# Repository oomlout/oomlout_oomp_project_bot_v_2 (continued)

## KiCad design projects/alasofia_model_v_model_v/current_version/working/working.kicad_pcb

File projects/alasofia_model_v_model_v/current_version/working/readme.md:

# model_v
 
## summary 
* id: alasofia_model_v_model_v
* user: alasofia
* name: model_v
* board: model_v
* repo: https://github.com/Alasofia/model-v
* src_file_repo_kicad_pcb: model-v.kicad_pcb
* src_file_repo_kicad_pcb_link: https://github.com/Alasofia/model-v/tree/main/model-v.kicad_pcb

* src_file_repo_sch: 
* src_file_repo_sch_link: https://github.com/Alasofia/model-v/tree/main/
* full details link: https://github.com/oomlout/oomlout_oomp_project_bot_v_2/tree/main/projects/alasofia_model_v_model_v/current_version/working  

## schematic  
  
[schematic (pdf)](working_schematic.pdf) 

## pcb  

[board (pdf)](working.pdf)  

## working_bom
| Id | Designator | Footprint | Quantity | Designation | Supplier and ref |  | None | 
| --- | --- | --- | --- | --- | --- | --- | --- | 
| 1 | K_42 | MXOnly-2.25U-ReversedStabilizers-NoLED | 1 | KEYSW |  |  | [''] | 
| 2 | K_37,K_13,K_47,K_39 | MXOnly-1.25U-NoLED | 4 | KEYSW |  |  | [''] | 
| 3 | K_6,K_32,K_50,K_48,K_18,K_31,K_20,K_22,K_33,K_30,K_7,K_15,K_17,K_49,K_26,K_36,K_8,K_2,K_11,K_5,K_9,K_1,K_10,K_16,K_14,K_35,K_34,K_46,K_40,K_28,K_3,K_38,K_29,K_21,K_27,K_23,K_19,K_4 | MXOnly-1U-NoLED | 38 | KEYSW |  |  | [''] | 
| 4 | K_44 | MXOnly-2U-ReversedStabilizers-NoLED | 1 | KEYSW |  |  | [''] | 
| 5 | K_12,K_25 | MXOnly-1.75U-NoLED | 2 | KEYSW |  |  | [''] | 
| 6 | K_41,K_45 | MXOnly-3U-ReversedStabilizers-NoLED | 2 | KEYSW |  |  | [''] | 
| 7 | K_24 | MXOnly-1.5U-NoLED | 1 | KEYSW |  |  | [''] | 
| 8 | K_43 | MXOnly-6.25U-ReversedStabilizers-NoLED | 1 | KEYSW |  |  | [''] | 
| 9 | SW1 | SW_Push_SPST_NO_Alps_SKRK | 1 | SW_Push |  |  | [''] | 
| 10 | D_12,D_36,D_46,D_44,D_14,D_20,D_10,D_22,D_13,D_38,D_33,D_45,D_6,D_32,D_2,D_39,D_11,D_37,D_30,D_27,D_18,D_24,D_42,D_17,D_23,D_41,D_9,D_8,D_29,D_31,D_15,D_16,D_1,D_3,D_28,D_7,D_4,D_5,D_19,D_34,D_25,D_21,D_43,D_35,D_40,D_26 | D_SOD-123 | 46 | D |  |  | [''] | 
| 11 | F1 | Fuse_1206_3216Metric | 1 | 500mA |  |  | [''] | 
| 12 | U2 | SOT143B | 1 | PRTR5V0U2X |  |  | [''] | 
| 13 | USB1 | HRO-TYPE-C-31-M-12-Assembly | 1 | HRO-TYPE-C-31-M-12 |  |  | [''] | 
| 14 | R4,R3 | R_0603_1608Metric | 2 | 22 |  |  | [''] | 
| 15 | R2,R1 | R_0603_1608Metric | 2 | 5.1k |  |  | [''] | 
| 16 | C2,C3,C4,C5,C6 | C_0603_1608Metric | 5 | 0.1uF |  |  | [''] | 
| 17 | C7 | C_0603_1608Metric | 1 | 1uF |  |  | [''] | 
| 18 | C8,C9 | C_0603_1608Metric | 2 | 22pF |  |  | [''] | 
| 19 | Y1 | Crystal_SMD_3225-4Pin_3.2x2.5mm | 1 | 16MHz |  |  | [''] | 
| 20 | U1 | QFN-44-1EP_7x7mm_P0.5mm_EP5.2x5.2mm | 1 | ATmega32U4-MU |  |  | [''] | 
| 21 | C1 | C_0603_1608Metric | 1 | 10uF |  |  | [''] | 
| 22 | R5,R6 | R_0603_1608Metric | 2 | 10k |  |  | [''] | 
| 23 | G*** | model-v | 1 | LOGO |  |  | [''] | 

## bom_schematic
| Ref | Qnty | Value | Cmp name | Footprint | Description | Vendor | DNP | 
| --- | --- | --- | --- | --- | --- | --- | --- | 
| C1 | 1 | 10uF | C_Small | Capacitor_SMD:C_0603_1608Metric | Unpolarized capacitor, small symbol |  |  | 
| C2, C3, C4, C5, C6 | 5 | 0.1uF | C_Small | Capacitor_SMD:C_0603_1608Metric | Unpolarized capacitor, small symbol |  |  | 
| C7 | 1 | 1uF | C_Small | Capacitor_SMD:C_0603_1608Metric | Unpolarized capacitor, small symbol |  |  | 
| C8, C9 | 2 | 22pF | C_Small | Capacitor_SMD:C_0603_1608Metric | Unpolarized capacitor, small symbol |  |  | 
| D_1, D_2, D_3, D_4, D_5, D_6, D_7, D_8, D_9, D_10, D_11, D_12, D_13, D_14, D_15, D_16, D_17, D_18, D_19, D_20, D_21, D_22, D_23, D_24, D_25, D_26, D_27, D_28, D_29, D_30, D_31, D_32, D_33, D_34, D_35, D_36, D_37, D_38, D_39, D_40, D_41, D_42, D_43, D_44, D_45, D_46 | 46 | D | D_Small | Diode_SMD:D_SOD-123 | Diode, small symbol |  |  | 
| F1 | 1 | 500mA | Polyfuse_Small | Fuse:Fuse_1206_3216Metric | Resettable fuse, polymeric positive temperature coefficient, small symbol |  |  | 
| K_1, K_2, K_3, K_4, K_5, K_6, K_7, K_8, K_9, K_10, K_11, K_14, K_15, K_16, K_17, K_18, K_19, K_20, K_21, K_22, K_23, K_26, K_27, K_28, K_29, K_30, K_31, K_32, K_33, K_34, K_35, K_36, K_38, K_40, K_46, K_48, K_49, K_50 | 38 | KEYSW | MX-NoLED | MX_Only:MXOnly-1U-NoLED |  |  |  | 
| K_12, K_25 | 2 | KEYSW | MX-NoLED | MX_Only:MXOnly-1.75U-NoLED |  |  |  | 
| K_13, K_37, K_39, K_47 | 4 | KEYSW | MX-NoLED | MX_Only:MXOnly-1.25U-NoLED |  |  |  | 
| K_24 | 1 | KEYSW | MX-NoLED | MX_Only:MXOnly-1.5U-NoLED |  |  |  | 
| K_41, K_45 | 2 | KEYSW | MX-NoLED | MX_Only:MXOnly-3U-ReversedStabilizers-NoLED |  |  |  | 
| K_42 | 1 | KEYSW | MX-NoLED | MX_Only:MXOnly-2.25U-ReversedStabilizers-NoLED |  |  |  | 
| K_43 | 1 | KEYSW | MX-NoLED | MX_Only:MXOnly-6.25U-ReversedStabilizers-NoLED |  |  |  | 
| K_44 | 1 | KEYSW | MX-NoLED | MX_Only:MXOnly-2U-ReversedStabilizers-NoLED |  |  |  | 
| R1, R2 | 2 | 5.1k | R_Small | Resistor_SMD:R_0603_1608Metric | Resistor, small symbol |  |  | 
| R3, R4 | 2 | 22 | R_Small | Resistor_SMD:R_0603_1608Metric | Resistor, small symbol |  |  | 
| R5, R6 | 2 | 10k | R_Small | Resistor_SMD:R_0603_1608Metric | Resistor, small symbol |  |  | 
| SW1 | 1 | SW_Push | SW_Push | Button_Switch_SMD:SW_Push_SPST_NO_Alps_SKRK | Push button switch, generic, two pins |  |  | 
| U1 | 1 | ATmega32U4-MU | ATmega32U4-MU-MCU_Microchip_ATmega | Package_DFN_QFN:QFN-44-1EP_7x7mm_P0.5mm_EP5.2x5.2mm |  |  |  | 
| U2 | 1 | PRTR5V0U2X | PRTR5V0U2X | random-keyboard-parts:SOT143B |  |  |  | 
| USB1 | 1 | HRO-TYPE-C-31-M-12 | HRO-TYPE-C-31-M-12 | Type-C:HRO-TYPE-C-31-M-12-Assembly |  |  |  | 
| Y1 | 1 | 16MHz | Crystal_GND24_Small | Crystal:Crystal_SMD_3225-4Pin_3.2x2.5mm | Four pin crystal, GND on pins 2 and 4, small symbol |  |  |

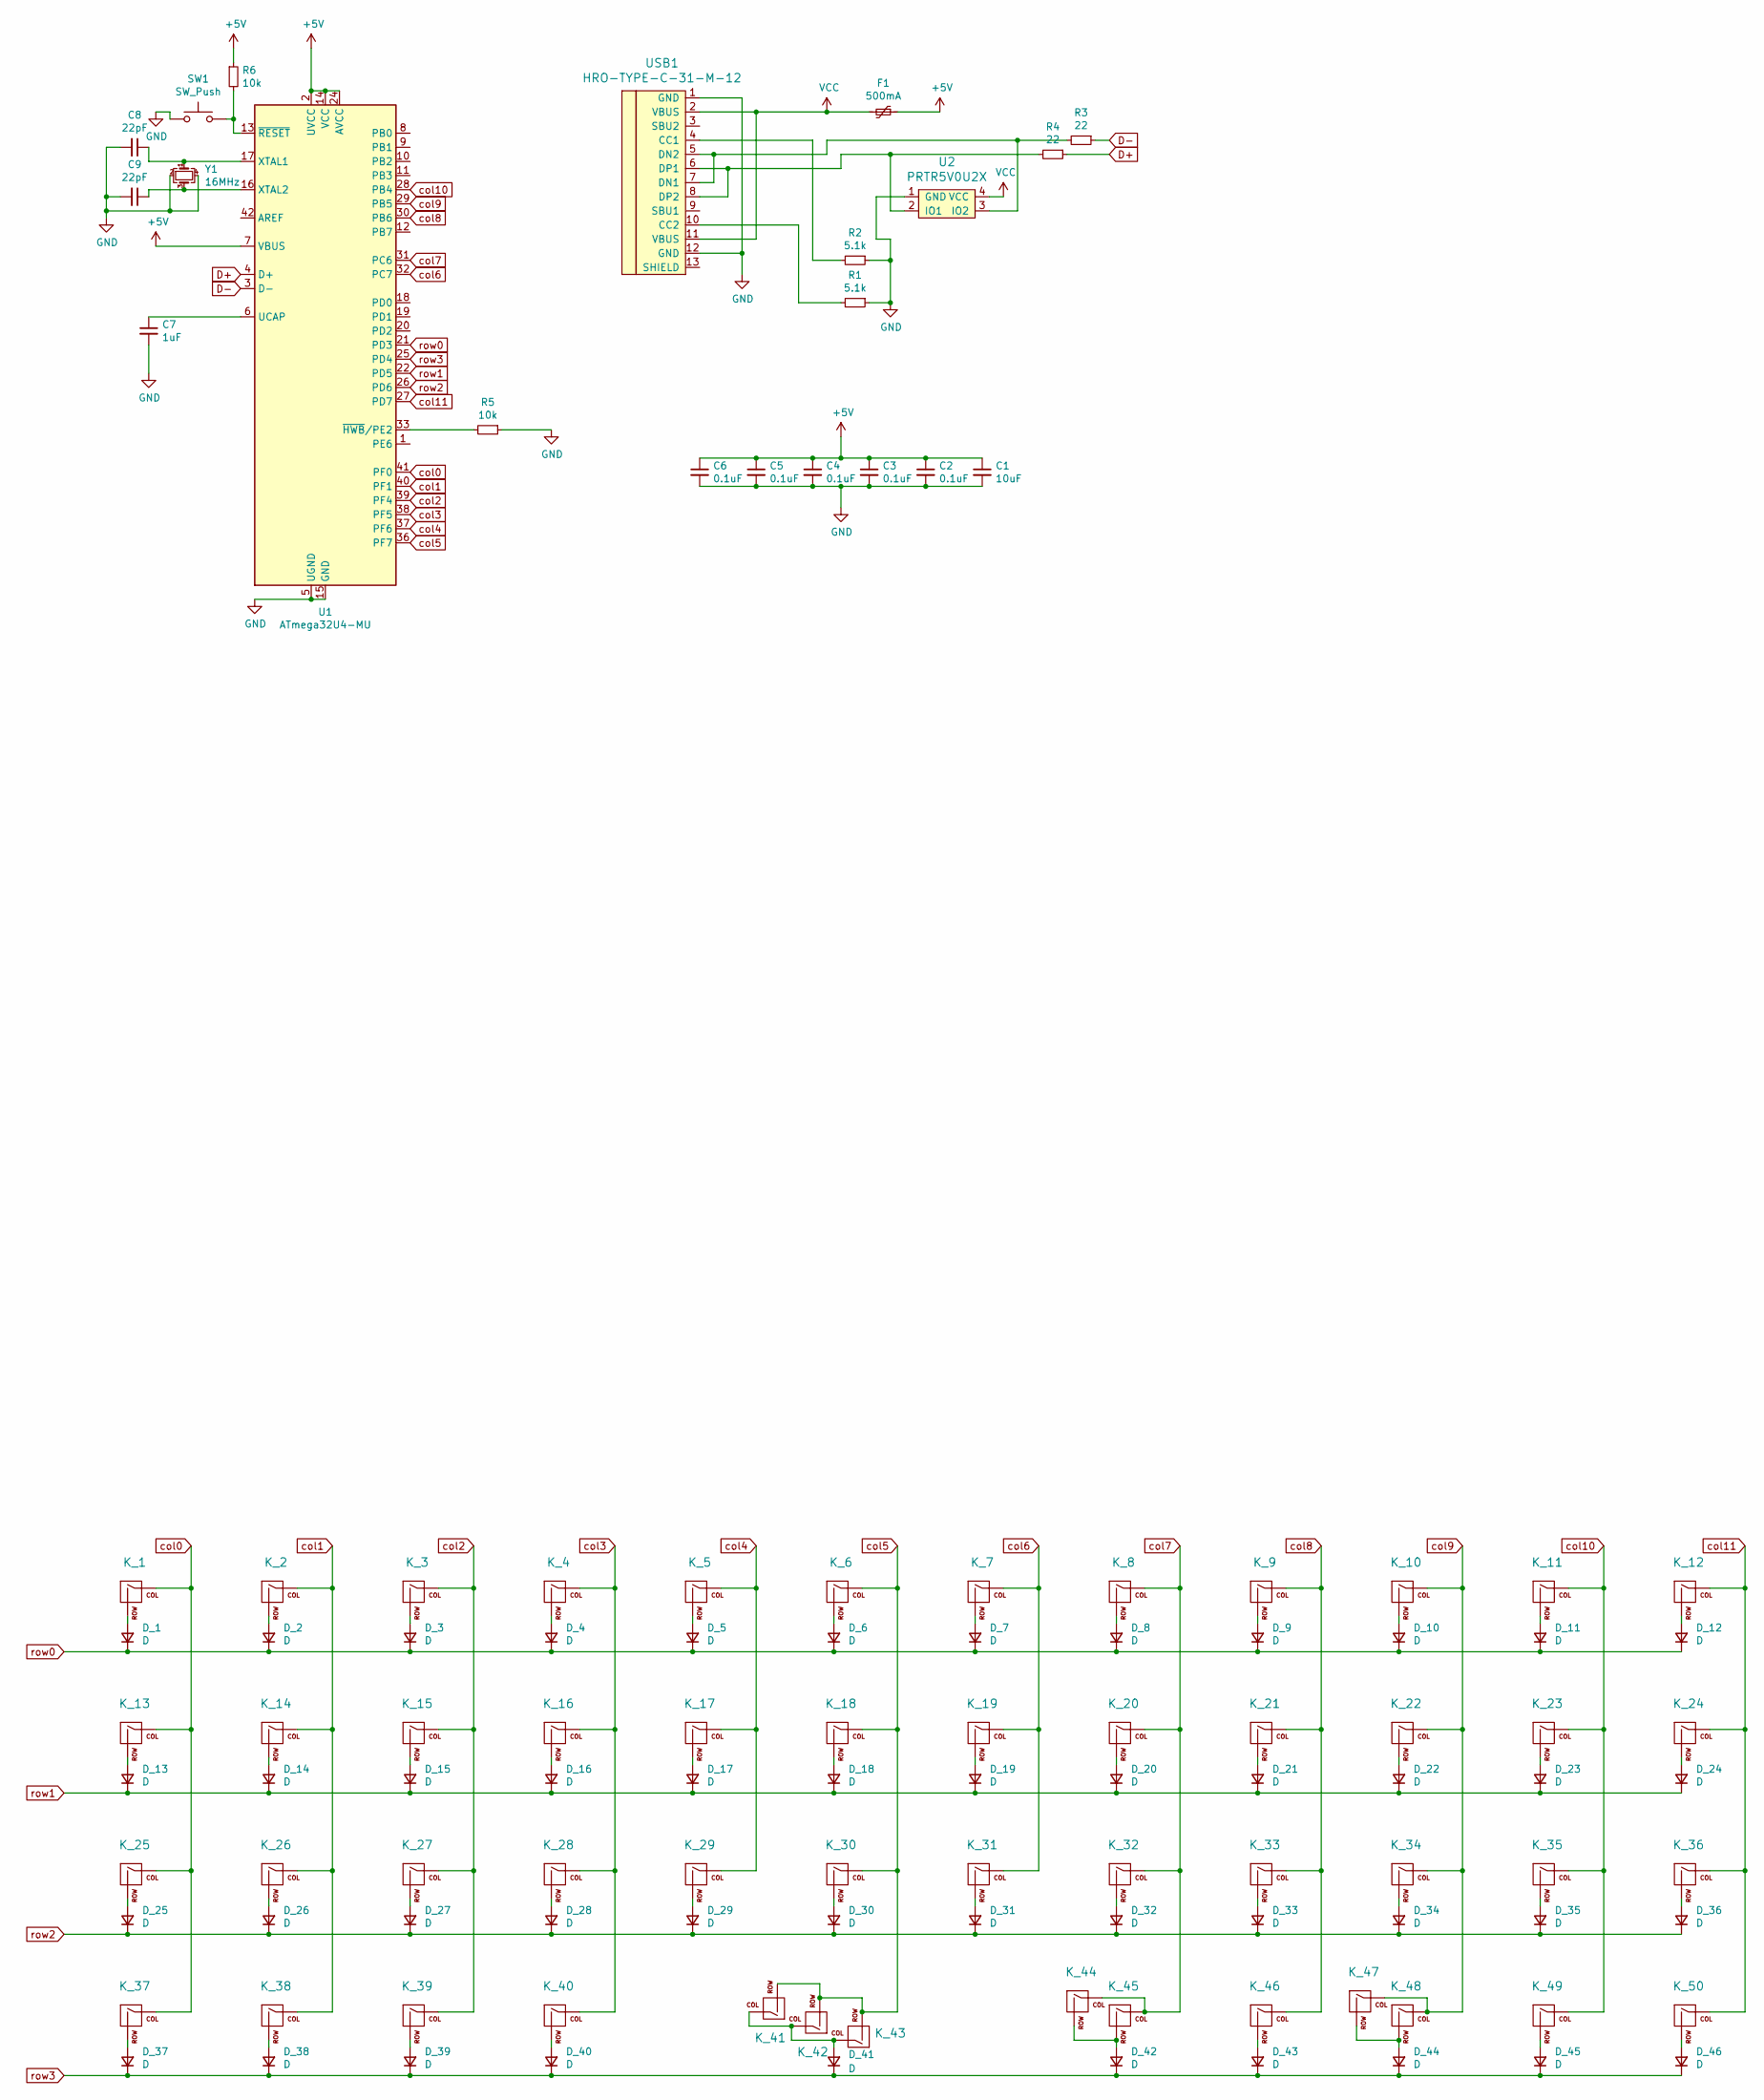
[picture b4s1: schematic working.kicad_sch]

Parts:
C1: 10uF; C_0603_1608Metric
C2, C3, C4, C5, C6: 0.1uF; C_0603_1608Metric
C7: 1uF; C_0603_1608Metric
C8, C9: 22pF; C_0603_1608Metric
D_1, D_2, D_3, D_4, D_5, D_6, D_7, D_8, D_9, D_10, D_11, D_12, D_13, D_14, D_15, D_16, D_17, D_18, D_19, D_20, D_21, D_22, D_23, D_24, D_25, D_26, D_27, D_28, D_29, D_30, D_31, D_32, D_33, D_34, D_35, D_36, D_37, D_38, D_39, D_40, D_41, D_42, D_43, D_44, D_45, D_46: D; D_SOD-123
F1: 500mA; Fuse_1206_3216Metric
K_1, K_2, K_3, K_4, K_5, K_6, K_7, K_8, K_9, K_10, K_11, K_14, K_15, K_16, K_17, K_18, K_19, K_20, K_21, K_22, K_23, K_26, K_27, K_28, K_29, K_30, K_31, K_32, K_33, K_34, K_35, K_36, K_38, K_40, K_46, K_48, K_49, K_50: KEYSW; MXOnly-1U-NoLED
K_12, K_25: KEYSW; MXOnly-1.75U-NoLED
K_13, K_37, K_39, K_47: KEYSW; MXOnly-1.25U-NoLED
K_24: KEYSW; MXOnly-1.5U-NoLED
K_41, K_45: KEYSW; MXOnly-3U-ReversedStabilizers-NoLED
K_42: KEYSW; MXOnly-2.25U-ReversedStabilizers-NoLED
K_43: KEYSW; MXOnly-6.25U-ReversedStabilizers-NoLED
K_44: KEYSW; MXOnly-2U-ReversedStabilizers-NoLED
R1, R2: 5.1k; R_0603_1608Metric
R3, R4: 22; R_0603_1608Metric
R5, R6: 10k; R_0603_1608Metric
SW1: SW_Push; SW_Push_SPST_NO_Alps_SKRK
U1: ATmega32U4-MU; QFN-44-1EP_7x7mm_P0.5mm_EP5.2x5.2mm
U2: PRTR5V0U2X; SOT143B
USB1: HRO-TYPE-C-31-M-12; HRO-TYPE-C-31-M-12-Assembly
Y1: 16MHz; Crystal_SMD_3225-4Pin_3.2x2.5mm

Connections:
+5V: C1.1, C2.1, C3.1, C4.1, C5.1, C6.1, F1.1, R6.1, U1.2 (UVCC), U1.7 (VBUS), U1.14 (VCC), U1.24 (AVCC), U1.34 (VCC), U1.44 (AVCC)
D+: R4.1, U1.4 (D+)
D-: R3.1, U1.3 (D-)
GND: C1.2, C2.2, C3.2, C4.2, C5.2, C6.2, C7.2, C8.2, C9.2, R1.1, R2.1, R5.1, SW1.1, U1.5 (UGND), U1.15 (GND), U1.23 (GND), U1.35 (GND), U1.43 (GND), U1.45 (GND), U2.1 (GND), USB1.1 (GND), USB1.12 (GND), Y1.2, Y1.4
unnamed: C7.1, U1.6 (UCAP)
unnamed: C8.1, U1.17 (XTAL1), Y1.1
unnamed: C9.1, U1.16 (XTAL2), Y1.3
unnamed: D_1.2 (A), K_1.2 (ROW)
unnamed: D_2.2 (A), K_2.2 (ROW)
unnamed: D_3.2 (A), K_3.2 (ROW)
unnamed: D_4.2 (A), K_4.2 (ROW)
unnamed: D_5.2 (A), K_5.2 (ROW)
unnamed: D_6.2 (A), K_6.2 (ROW)
unnamed: D_7.2 (A), K_7.2 (ROW)
unnamed: D_8.2 (A), K_8.2 (ROW)
unnamed: D_9.2 (A), K_9.2 (ROW)
unnamed: D_10.2 (A), K_10.2 (ROW)
unnamed: D_11.2 (A), K_11.2 (ROW)
unnamed: D_12.2 (A), K_12.2 (ROW)
unnamed: D_13.2 (A), K_13.2 (ROW)
unnamed: D_14.2 (A), K_14.2 (ROW)
unnamed: D_15.2 (A), K_15.2 (ROW)
unnamed: D_16.2 (A), K_16.2 (ROW)
unnamed: D_17.2 (A), K_17.2 (ROW)
unnamed: D_18.2 (A), K_18.2 (ROW)
unnamed: D_19.2 (A), K_19.2 (ROW)
unnamed: D_20.2 (A), K_20.2 (ROW)
unnamed: D_21.2 (A), K_21.2 (ROW)
unnamed: D_22.2 (A), K_22.2 (ROW)
unnamed: D_23.2 (A), K_23.2 (ROW)
unnamed: D_24.2 (A), K_24.2 (ROW)
unnamed: D_25.2 (A), K_25.2 (ROW)
unnamed: D_26.2 (A), K_26.2 (ROW)
unnamed: D_27.2 (A), K_27.2 (ROW)
unnamed: D_28.2 (A), K_28.2 (ROW)
unnamed: D_29.2 (A), K_29.2 (ROW)
unnamed: D_30.2 (A), K_30.2 (ROW)
unnamed: D_31.2 (A), K_31.2 (ROW)
unnamed: D_32.2 (A), K_32.2 (ROW)
unnamed: D_33.2 (A), K_33.2 (ROW)
unnamed: D_34.2 (A), K_34.2 (ROW)
unnamed: D_35.2 (A), K_35.2 (ROW)
unnamed: D_36.2 (A), K_36.2 (ROW)
unnamed: D_37.2 (A), K_37.2 (ROW)
unnamed: D_38.2 (A), K_38.2 (ROW)
unnamed: D_39.2 (A), K_39.2 (ROW)
unnamed: D_40.2 (A), K_40.2 (ROW)
unnamed: D_41.2 (A), K_41.1 (COL), K_42.1 (COL), K_43.1 (COL)
unnamed: D_42.2 (A), K_44.2 (ROW), K_45.2 (ROW)
unnamed: D_43.2 (A), K_46.2 (ROW)
unnamed: D_44.2 (A), K_47.2 (ROW), K_48.2 (ROW)
unnamed: D_45.2 (A), K_49.2 (ROW)
unnamed: D_46.2 (A), K_50.2 (ROW)
unnamed: R1.2, USB1.10 (CC2)
unnamed: R2.2, USB1.4 (CC1)
unnamed: R3.2, U2.3 (IO2), USB1.5 (DN2), USB1.7 (DN1)
unnamed: R4.2, U2.2 (IO1), USB1.6 (DP1), USB1.8 (DP2)
unnamed: R5.2, U1.33 (~HWB/PE2)
unnamed: R6.2, SW1.2, U1.13 (~RESET)
VCC: F1.2, U2.4 (VCC), USB1.2 (VBUS), USB1.11 (VBUS)
col0: K_1.1 (COL), K_13.1 (COL), K_25.1 (COL), K_37.1 (COL), U1.41 (PF0)
col1: K_2.1 (COL), K_14.1 (COL), K_26.1 (COL), K_38.1 (COL), U1.40 (PF1)
col2: K_3.1 (COL), K_15.1 (COL), K_27.1 (COL), K_39.1 (COL), U1.39 (PF4)
col3: K_4.1 (COL), K_16.1 (COL), K_28.1 (COL), K_40.1 (COL), U1.38 (PF5)
col4: K_5.1 (COL), K_17.1 (COL), K_29.1 (COL), U1.37 (PF6)
col5: K_6.1 (COL), K_18.1 (COL), K_30.1 (COL), K_41.2 (ROW), K_42.2 (ROW), K_43.2 (ROW), U1.36 (PF7)
col6: K_7.1 (COL), K_19.1 (COL), K_31.1 (COL), U1.32 (PC7)
col7: K_8.1 (COL), K_20.1 (COL), K_32.1 (COL), K_44.1 (COL), K_45.1 (COL), U1.31 (PC6)
col8: K_9.1 (COL), K_21.1 (COL), K_33.1 (COL), K_46.1 (COL), U1.30 (PB6)
col9: K_10.1 (COL), K_22.1 (COL), K_34.1 (COL), K_47.1 (COL), K_48.1 (COL), U1.29 (PB5)
col10: K_11.1 (COL), K_23.1 (COL), K_35.1 (COL), K_49.1 (COL), U1.28 (PB4)
col11: K_12.1 (COL), K_24.1 (COL), K_36.1 (COL), K_50.1 (COL), U1.27 (PD7)
row0: D_1.1 (K), D_2.1 (K), D_3.1 (K), D_4.1 (K), D_5.1 (K), D_6.1 (K), D_7.1 (K), D_8.1 (K), D_9.1 (K), D_10.1 (K), D_11.1 (K), D_12.1 (K), U1.21 (PD3)
row1: D_13.1 (K), D_14.1 (K), D_15.1 (K), D_16.1 (K), D_17.1 (K), D_18.1 (K), D_19.1 (K), D_20.1 (K), D_21.1 (K), D_22.1 (K), D_23.1 (K), D_24.1 (K), U1.22 (PD5)
row2: D_25.1 (K), D_26.1 (K), D_27.1 (K), D_28.1 (K), D_29.1 (K), D_30.1 (K), D_31.1 (K), D_32.1 (K), D_33.1 (K), D_34.1 (K), D_35.1 (K), D_36.1 (K), U1.26 (PD6)
row3: D_37.1 (K), D_38.1 (K), D_39.1 (K), D_40.1 (K), D_41.1 (K), D_42.1 (K), D_43.1 (K), D_44.1 (K), D_45.1 (K), D_46.1 (K), U1.25 (PD4)

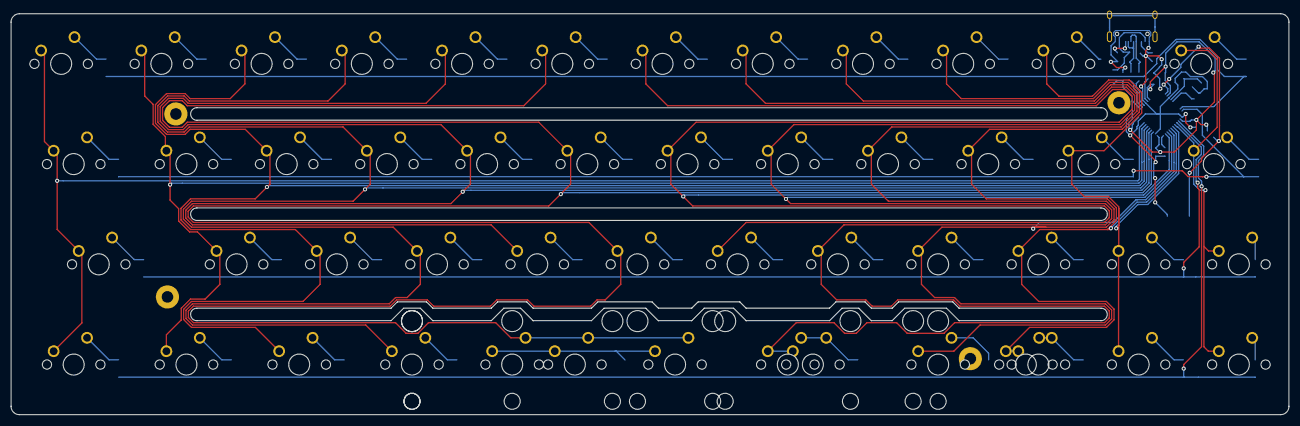
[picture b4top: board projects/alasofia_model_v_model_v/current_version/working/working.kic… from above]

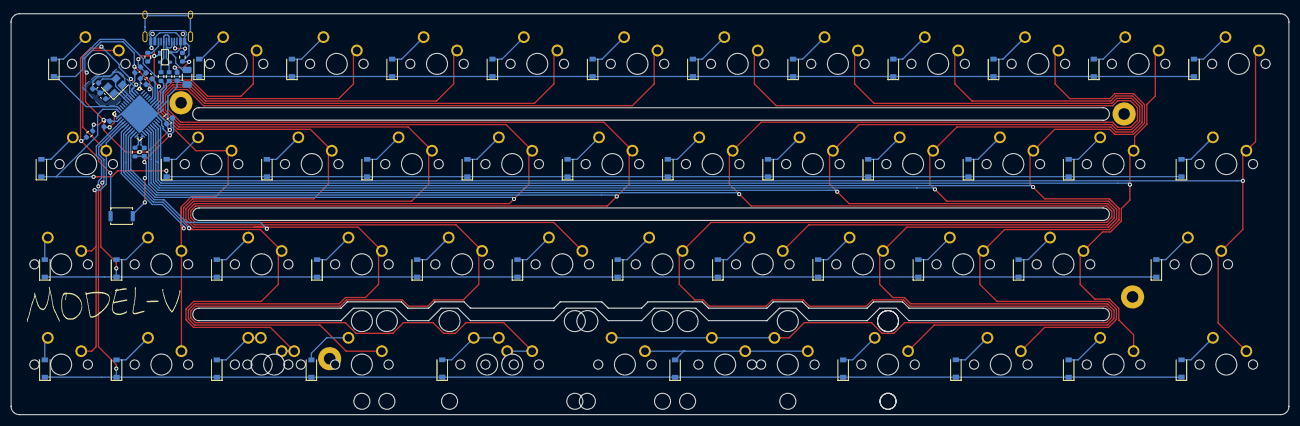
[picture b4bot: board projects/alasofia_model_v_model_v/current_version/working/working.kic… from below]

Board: 2 copper layers, 242.9 x 76.2 mm, 121 parts (67 on the bottom side), 76 nets.

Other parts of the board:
H1, H2, H6, H6#2: MountingHole_Pad; MountingHole_2.2mm_M2_Pad

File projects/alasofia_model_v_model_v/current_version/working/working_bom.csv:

"Id";"Designator";"Footprint";"Quantity";"Designation";"Supplier and ref";
1;"K_42";"MXOnly-2.25U-ReversedStabilizers-NoLED";1;"KEYSW";;;
2;"K_37,K_13,K_47,K_39";"MXOnly-1.25U-NoLED";4;"KEYSW";;;
3;"K_6,K_32,K_50,K_48,K_18,K_31,K_20,K_22,K_33,K_30,K_7,K_15,K_17,K_49,K_26,K_36,K_8,K_2,K_11,K_5,K_9,K_1,K_10,K_16,K_14,K_35,K_34,K_46,K_40,K_28,K_3,K_38,K_29,K_21,K_27,K_23,K_19,K_4";"MXOnly-1U-NoLED";38;"KEYSW";;;
4;"K_44";"MXOnly-2U-ReversedStabilizers-NoLED";1;"KEYSW";;;
5;"K_12,K_25";"MXOnly-1.75U-NoLED";2;"KEYSW";;;
6;"K_41,K_45";"MXOnly-3U-ReversedStabilizers-NoLED";2;"KEYSW";;;
7;"K_24";"MXOnly-1.5U-NoLED";1;"KEYSW";;;
8;"K_43";"MXOnly-6.25U-ReversedStabilizers-NoLED";1;"KEYSW";;;
9;"SW1";"SW_Push_SPST_NO_Alps_SKRK";1;"SW_Push";;;
10;"D_12,D_36,D_46,D_44,D_14,D_20,D_10,D_22,D_13,D_38,D_33,D_45,D_6,D_32,D_2,D_39,D_11,D_37,D_30,D_27,D_18,D_24,D_42,D_17,D_23,D_41,D_9,D_8,D_29,D_31,D_15,D_16,D_1,D_3,D_28,D_7,D_4,D_5,D_19,D_34,D_25,D_21,D_43,D_35,D_40,D_26";"D_SOD-123";46;"D";;;
11;"F1";"Fuse_1206_3216Metric";1;"500mA";;;
12;"U2";"SOT143B";1;"PRTR5V0U2X";;;
13;"USB1";"HRO-TYPE-C-31-M-12-Assembly";1;"HRO-TYPE-C-31-M-12";;;
14;"R4,R3";"R_0603_1608Metric";2;"22";;;
15;"R2,R1";"R_0603_1608Metric";2;"5.1k";;;
16;"C2,C3,C4,C5,C6";"C_0603_1608Metric";5;"0.1uF";;;
17;"C7";"C_0603_1608Metric";1;"1uF";;;
18;"C8,C9";"C_0603_1608Metric";2;"22pF";;;
19;"Y1";"Crystal_SMD_3225-4Pin_3.2x2.5mm";1;"16MHz";;;
20;"U1";"QFN-44-1EP_7x7mm_P0.5mm_EP5.2x5.2mm";1;"ATmega32U4-MU";;;
21;"C1";"C_0603_1608Metric";1;"10uF";;;
22;"R5,R6";"R_0603_1608Metric";2;"10k";;;
23;"G***";"model-v";1;"LOGO";;;

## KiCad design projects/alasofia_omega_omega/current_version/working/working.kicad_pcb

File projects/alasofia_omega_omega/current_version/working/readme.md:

# omega
 
## summary 
* id: alasofia_omega_omega
* user: alasofia
* name: omega
* board: omega
* repo: https://github.com/Alasofia/omega
* src_file_repo_kicad_pcb: omega_hotswap/omega.kicad_pcb
* src_file_repo_kicad_pcb_link: https://github.com/Alasofia/omega/tree/master/omega_hotswap/omega.kicad_pcb

* src_file_repo_sch: omega_hotswap/omega.sch
* src_file_repo_sch_link: https://github.com/Alasofia/omega/tree/master/omega_hotswap/omega.sch
* full details link: https://github.com/oomlout/oomlout_oomp_project_bot_v_2/tree/main/projects/alasofia_omega_omega/current_version/working  

## schematic  
  
[schematic (pdf)](working_schematic.pdf) 

## pcb  

[board (pdf)](working.pdf)  

## working_bom
| Id | Designator | Footprint | Quantity | Designation | Supplier and ref |  | None | 
| --- | --- | --- | --- | --- | --- | --- | --- | 
| 1 | D1,D7,D8,D9,D12,D13,D14,D15,D16,D17,D18,D19,D20,D21,D22,D23,D25,D26,D27,D28,D29,D24,D10,D6,D5,D4,D3,D2,D11 | Diode-Hybrid-Back | 29 | D_Small |  |  | [''] | 
| 2 | MX1,MX2,MX4,MX5,MX6,MX7,MX8,MX9,MX10,MX11,MX12,MX13,MX14,MX15,MX16,MX17,MX18,MX19,MX20,MX21,MX22,MX23,MX24,MX26,MX27,MX28,MX29,MX3 | MXOnly-1U-Hotswap | 28 | MX-NoLED |  |  | [''] | 
| 3 | MX25 | MXOnly-2U-Hotswap-ReversedStabilizers | 1 | MX-NoLED |  |  | [''] | 
| 4 | R1 | R_Axial_DIN0204_L3.6mm_D1.6mm_P5.08mm_Horizontal | 1 | 10k |  |  | [''] | 
| 5 | SW1 | SKQG-1155865 | 1 | SW_Push |  |  | [''] | 
| 6 | U1 | ProMicro | 1 | ProMicro |  |  | [''] | 

## bom_schematic
| Ref | Qnty | Value | Cmp name | Footprint | Description | Vendor | DNP | 
| --- | --- | --- | --- | --- | --- | --- | --- | 
| D1, D2, D3, D4, D5, D6, D7, D8, D9, D10, D11, D12, D13, D14, D15, D16, D17, D18, D19, D20, D21, D22, D23, D24, D25, D26, D27, D28, D29 | 29 | D_Small | D_Small | Keebio-Parts:Diode-Hybrid-Back | Diode, small symbol |  |  | 
| H1, H2, H3, H4 | 4 | MountingHole | MountingHole | MountingHole:MountingHole_2.2mm_M2_Pad | Mounting Hole without connection |  |  | 
| R1 | 1 | 10k | R_Small | Resistor_THT:R_Axial_DIN0204_L3.6mm_D1.6mm_P5.08mm_Horizontal | Resistor, small symbol |  |  | 
| SW1 | 1 | SW_Push | SW_Push | random-keyboard-parts:SKQG-1155865 | Push button switch, generic, two pins |  |  |

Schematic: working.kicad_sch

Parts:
D1, D2, D3, D4, D5, D6, D7, D8, D9, D10, D11, D12, D13, D14, D15, D16, D17, D18, D19, D20, D21, D22, D23, D24, D25, D26, D27, D28, D29: D_Small; Diode-Hybrid-Back
H1, H2, H3, H4: MountingHole; MountingHole_2.2mm_M2_Pad
MX1, MX2, MX3, MX4, MX5, MX6, MX7, MX8, MX9, MX10, MX11, MX12, MX13, MX14, MX15, MX16, MX17, MX18, MX19, MX20, MX21, MX22, MX23, MX24, MX26, MX27, MX28, MX29: MX-NoLED; MXOnly-1U-Hotswap
MX25: MX-NoLED; MXOnly-2U-Hotswap-ReversedStabilizers
R1: 10k; R_Axial_DIN0204_L3.6mm_D1.6mm_P5.08mm_Horizontal
SW1: SW_Push; SKQG-1155865
U1: ProMicro

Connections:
+5V: R1.1, U1.21
COL0: MX1.1, MX11.1, MX21.1, U1.20
COL1: MX2.1, MX12.1, MX22.1, U1.16
COL2: MX3.1, MX13.1, MX23.1, U1.15
COL3: MX4.1, MX14.1, MX24.1, U1.14
COL4: MX5.1, MX15.1, MX25.1, U1.13
COL5: MX6.1, MX16.1, U1.12
COL6: MX7.1, MX17.1, MX26.1, U1.11
COL7: MX8.1, MX18.1, MX27.1, U1.10
COL8: MX9.1, MX19.1, MX28.1, U1.9
COL9: MX10.1, MX20.1, MX29.1, U1.8
GND: SW1.2, U1.3, U1.4, U1.23
unnamed: D1.2 (A), MX1.2
unnamed: D2.2 (A), MX2.2
unnamed: D3.2 (A), MX3.2
unnamed: D4.2 (A), MX4.2
unnamed: D5.2 (A), MX5.2
unnamed: D6.2 (A), MX6.2
unnamed: D7.2 (A), MX7.2
unnamed: D8.2 (A), MX8.2
unnamed: D9.2 (A), MX9.2
unnamed: D10.2 (A), MX10.2
unnamed: D11.2 (A), MX11.2
unnamed: D12.2 (A), MX12.2
unnamed: D13.2 (A), MX13.2
unnamed: D14.2 (A), MX14.2
unnamed: D15.2 (A), MX15.2
unnamed: D16.2 (A), MX16.2
unnamed: D17.2 (A), MX17.2
unnamed: D18.2 (A), MX18.2
unnamed: D19.2 (A), MX19.2
unnamed: D20.2 (A), MX20.2
unnamed: D21.2 (A), MX21.2
unnamed: D22.2 (A), MX22.2
unnamed: D23.2 (A), MX23.2
unnamed: D24.2 (A), MX24.2
unnamed: D25.2 (A), MX25.2
unnamed: D26.2 (A), MX26.2
unnamed: D27.2 (A), MX27.2
unnamed: D28.2 (A), MX28.2
unnamed: D29.2 (A), MX29.2
unnamed: R1.2, SW1.1, U1.22
ROW0: D1.1 (K), D2.1 (K), D3.1 (K), D4.1 (K), D5.1 (K), D6.1 (K), D7.1 (K), D8.1 (K), D9.1 (K), D10.1 (K), U1.17
ROW1: D11.1 (K), D12.1 (K), D13.1 (K), D14.1 (K), D15.1 (K), D16.1 (K), D17.1 (K), D18.1 (K), D19.1 (K), D20.1 (K), U1.18
ROW2: D21.1 (K), D22.1 (K), D23.1 (K), D24.1 (K), D25.1 (K), D26.1 (K), D27.1 (K), D28.1 (K), D29.1 (K), U1.19

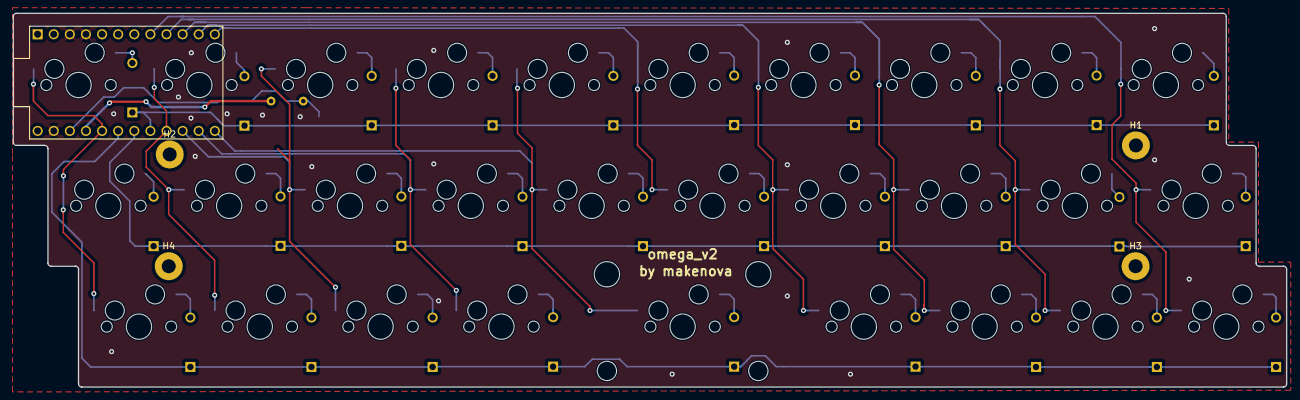
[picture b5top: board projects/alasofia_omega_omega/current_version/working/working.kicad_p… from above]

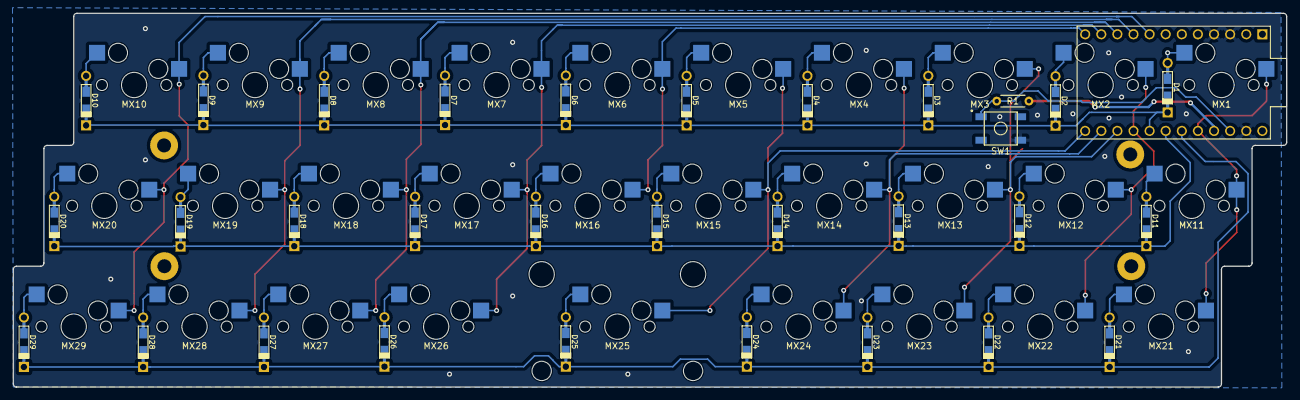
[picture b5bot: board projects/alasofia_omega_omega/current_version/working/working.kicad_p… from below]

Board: 2 copper layers, 200.8 x 58.9 mm, 65 parts (3 on the bottom side), 45 nets.
